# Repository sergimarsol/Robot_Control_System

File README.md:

# MSP430FR2355 Robot Control System

This repository contains the complete development of a robotic control system based on the MSP430FR2355 microcontroller. The project encompasses hardware design, embedded software development, real-time control implementation, and autonomous behavior strategies. All stages—from conceptual engineering to full system deployment—were carried out by a single author.

## Project Overview

The system enables robot control through multiple operational modes, leveraging a modular driver-based firmware architecture. It integrates input devices, actuators, and display components to provide both manual and autonomous control functionalities. The hardware was designed, assembled, debugged, and calibrated to ensure correct interaction among all peripherals.

### Control Modes
- **Joystick Mode**: Manual navigation using an analog joystick.
- **Light-Following Mode**: Robot movement directed toward the strongest detected light using LDR readings.
- **Line-Following Mode**: Ground sensor-based autonomous navigation via line detection.
- **Main Menu Interface**: LCD-driven user interface navigated using the joystick.

## Hardware Architecture

| Component | Description |
|-----------|-------------|
| MSP430FR2355 MCU | Core controller handling I2C, ADC, timers, GPIOs |
| 32.7KHz Crystal | Clock stabilization |
| SBW Connector | Programming and debugging interface |
| LCD 16x2 (I2C) | Displays system information and menu |
| Joystick | Directional input for manual control and navigation |
| LDR Sensors (ADC) | Detect light intensity for autonomous movement |
| Motor Driver (I2C) | Controls wheel motors for robot movement |
| RGB LEDs (I2C) | Status indication |
| ESP-01 Module (UART) | Planned Wi-Fi communication support |

## Software Architecture

The firmware was implemented with a modular structure to maximize maintainability and reusability.

| Module | Purpose |
|--------|---------|
| `main.c` | System initialization and main control loop |
| `timer.h` | Timer configuration, delays, millisecond counter ISR |
| `i2c.h` | I2C communication management and ISR |
| `lcd.h` | LCD initialization and text display functions |
| `leds.h` | RGB LED color control |
| `motors.h` | Motor control for direction and velocity |
| `joystick.h` | Joystick reading and movement triggering |
| `adc.h` | Light sensor acquisition and averaging |
| `sensors.h` | Line detection and autonomous path adjustment |

## Proposed Repository Structure

```
MSP430-Robot-Control-System
├── hardware/
│   ├── SergiMarsol_Gerber/                  # Gerber manufacturing outputs
│   ├── SergiMarsol_projecte_MISE.kicad_pro  # KiCad project file
│   ├── SergiMarsol_projecte_MISE.kicad_sch  # Schematic design
│   ├── SergiMarsol_projecte_MISE.kicad_pcb  # PCB layout
│   ├── SergiMarsol_projecte_MISE-backups/   # KiCad auto-backups
│   ├── SergiMarsol_projecte_MISE.kicad_prl  # KiCad project local settings
│   ├── fp-info-cache                        # Footprint cache
│   └── fp-lib-table                         # Footprint library table
├── firmware/
│   ├── ADC.c
│   ├── ADC.h
│   ├── i2c.c
│   ├── i2c.h
│   ├── joystick.c
│   ├── joystick.h
│   ├── lcd.c
│   ├── lcd.h
│   ├── leds.c
│   ├── leds.h
│   ├── motors.c
│   ├── motors.h
│   ├── sensors.c
│   ├── sensors.h
│   ├── timer.c
│   ├── timer.h
│   ├── main.c
│   ├── lnk_msp430fr2355.cmd                 # Linker command file
│   ├── Debug/                               # Compilation artifacts
│   └── targetConfigs/                       # MCU target configuration files
├── documents/
│   └── presentation.pdf                       # Final presentation of the project (in Catalan)
└── README.md
```

## Development Highlights

| Phase | Achievement |
|-------|------------|
| Concept Engineering | Block diagrams, requirements, planning |
| Hardware Implementation | Complete schematic design, assembly, correction of ADC pin assignments |
| Software Implementation | Driver-based structure enabling scalability |
| Debugging | Systematic validation using modular subsystem tests |
| Optional Expansion | UART-based Wi-Fi communication ready for future phases |

## Conclusion

The project demonstrates an end-to-end realization of an embedded robotic control system, showcasing microcontroller-based hardware integration, real-time firmware development, and autonomous control strategies. It serves as an excellent reference for modular embedded system design using the MSP430 ecosystem.

---

For future developments, planned features include remote control via Wi-Fi, telemetry reporting, and enhanced control algorithms such as PID for smoother autonomous navigation.

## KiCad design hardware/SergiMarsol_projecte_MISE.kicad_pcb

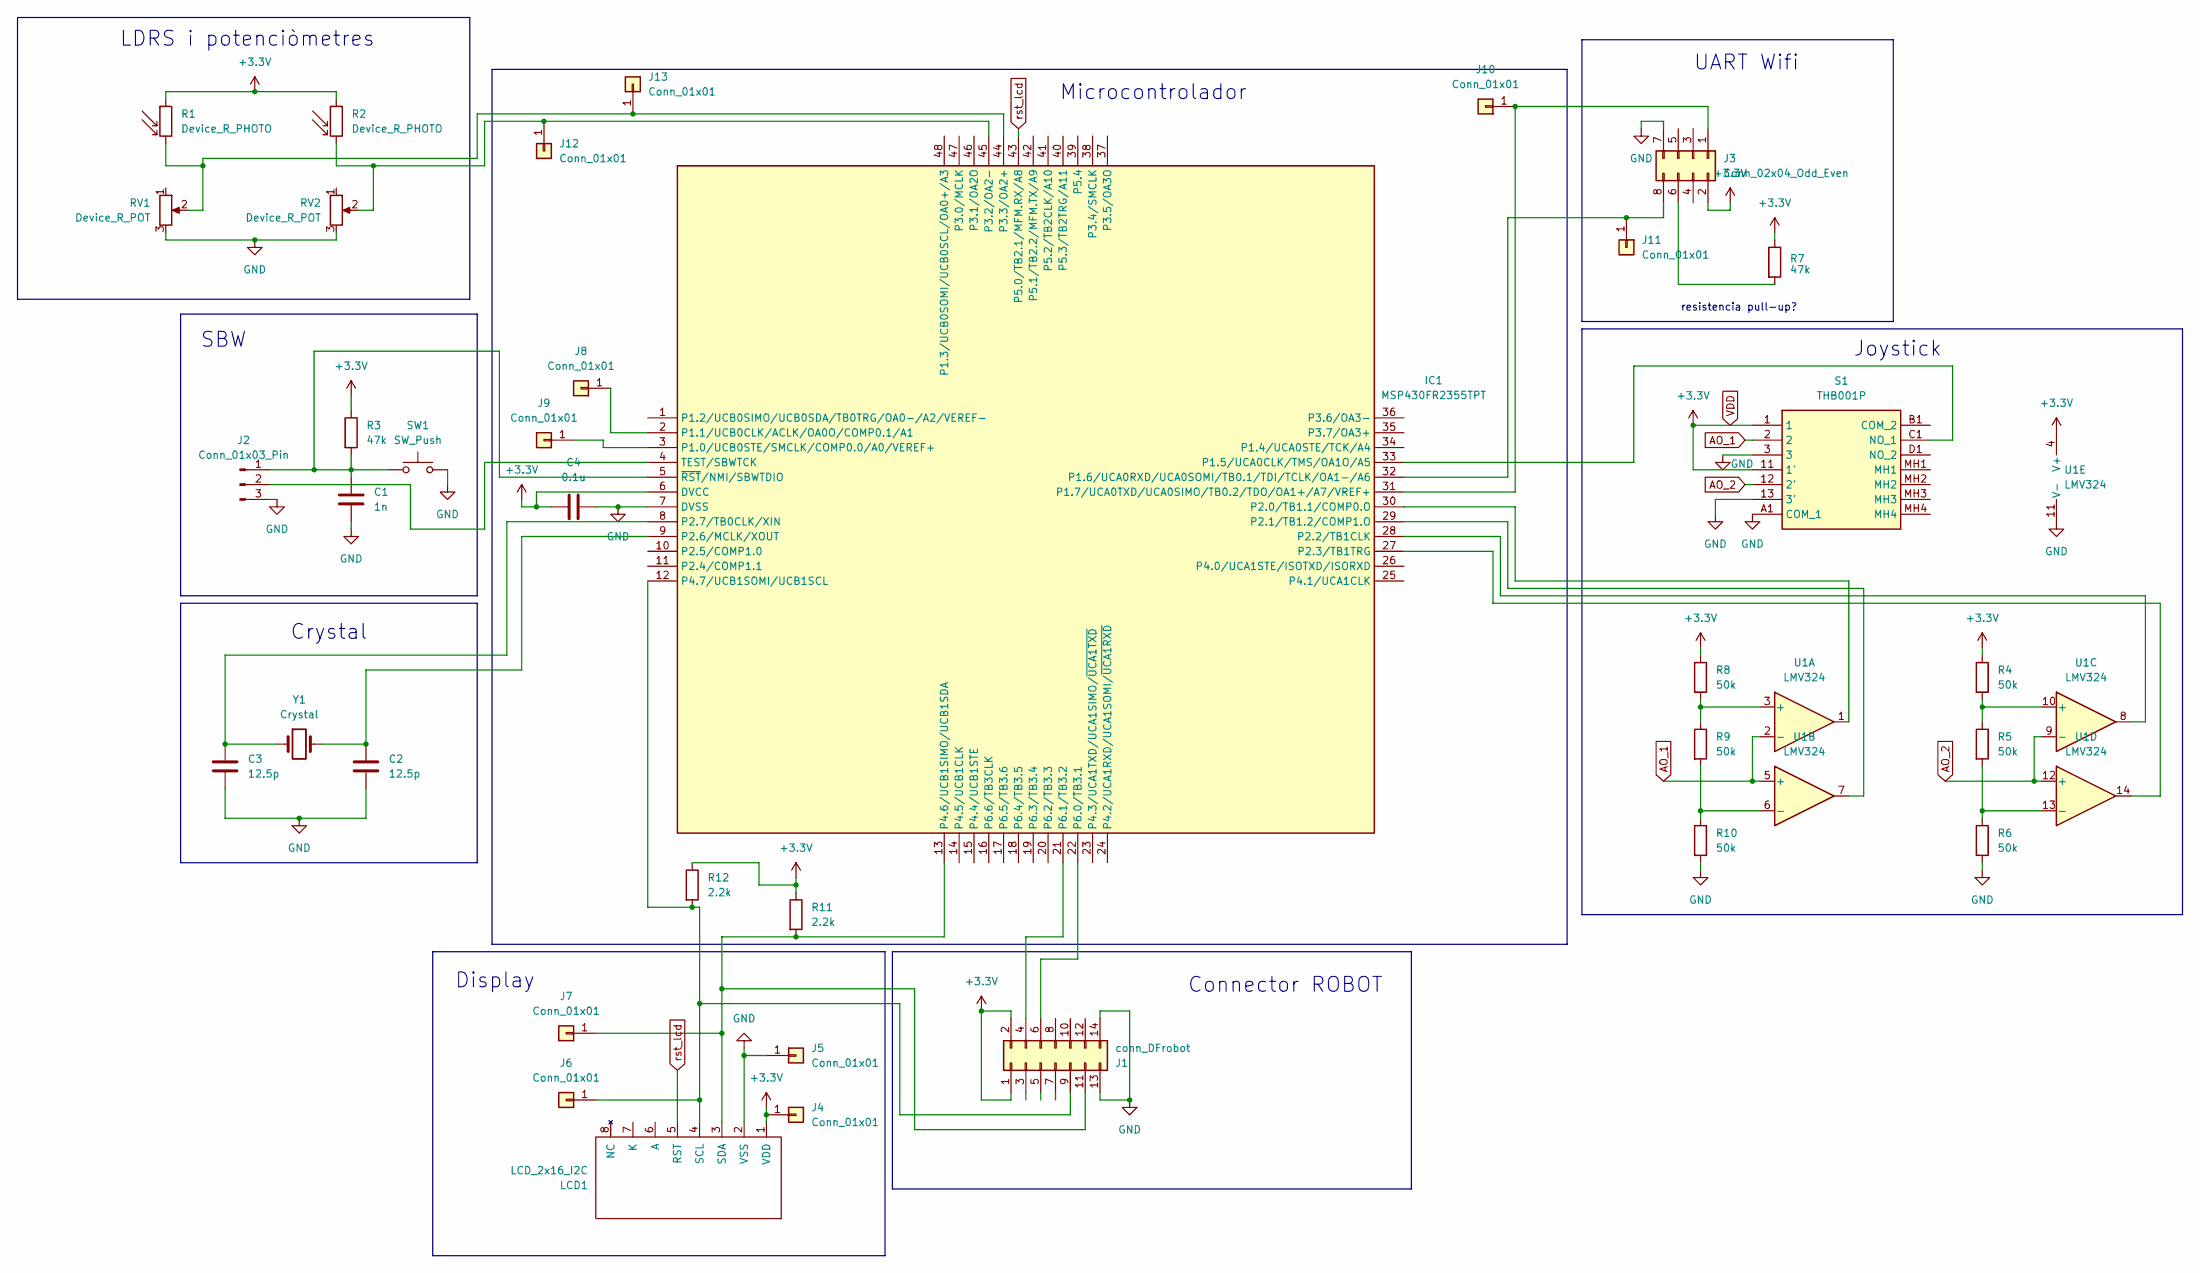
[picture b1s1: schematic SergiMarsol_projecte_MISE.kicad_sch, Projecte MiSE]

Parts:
C1: 1n; C_0805_2012Metric
C2, C3: 12.5p; C_0805_2012Metric
C4: 0.1u; C_0805_2012Metric
IC1: MSP430FR2355TPT; QFP50P900X900X160-48N; Manufacturer_Part_Number MSP430FR2355TPT; Mouser Part Number 595-MSP430FR2355TPT
J1: conn_DFrobot
J2: Conn_01x03_Pin; PinHeader_1x03_P2.54mm_Vertical
J3: Conn_02x04_Odd_Even; PinHeader_2x04_P2.54mm_Vertical
J4, J5, J6, J7, J8, J9, J10, J11, J12, J13: Conn_01x01; PinHeader_1x01_P2.54mm_Vertical
LCD1: LCD_2x16_I2C; LCD_2x16_I2C(Midas)
R1, R2: Device_R_PHOTO; LDR
R3, R7: 47k; R_0805_2012Metric
R4, R5, R6, R8, R9, R10: 50k; R_0805_2012Metric
R11, R12: 2.2k; R_0805_2012Metric
RV1, RV2: Device_R_POT; Trimmer_MiSE
S1: THB001P; Manufacturer_Part_Number THB001P; Mouser Part Number 611-THB001P
SW1: SW_Push; SW_PUSH_6mm_H4.3mm
U1: LMV324; SOIC127P600X175-14N
Y1: Crystal; XTAL_ECS-.327-8-14

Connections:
AO_1: S1.2, U1.2 (-), U1.5 (+)
AO_2: S1.12 (2'), U1.9 (-), U1.12 (+)
GND: C1.2, C2.2, C3.2, C4.2, IC1.7 (DVSS), J1.13, J1.14, J2.3, J3.7, J5.1, LCD1.2 (VSS), R6.2, R10.2, RV1.3, RV2.3, S1.3, S1.13 (3'), S1.A1 (COM_1), SW1.2, U1.11 (V-)
unnamed: IC1.3 (P1.0/UCB0STE/SMCLK/COMP0.0/A0/VEREF+), J9.1
unnamed: IC1.2 (P1.1/UCB0CLK/ACLK/OA0O/COMP0.1/A1), J8.1
unnamed: IC1.33 (P1.5/UCA0CLK/TMS/OA1O/A5), S1.C1 (NO_1)
unnamed: IC1.32 (P1.6/UCA0RXD/UCA0SOMI/TB0.1/TDI/TCLK/OA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), J3.8, J11.1
unnamed: IC1.31 (P1.7/UCA0TXD/UCA0SIMO/TB0.2/TDO/OA1+/A7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), J3.1, J10.1
unnamed: IC1.30 (P2.0/TB1.1/COMP0.O), U1.1
unnamed: IC1.29 (P2.1/TB1.2/COMP1.O), U1.7
unnamed: IC1.28 (P2.2/TB1CLK), U1.8
unnamed: IC1.27 (P2.3/TB1TRG), U1.14
unnamed: C2.1, IC1.9 (P2.6/MCLK/XOUT), Y1.2
unnamed: C3.1, IC1.8 (P2.7/TB0CLK/XIN), Y1.1
unnamed: IC1.45 (P3.2/OA2-), J12.1, R2.2, RV2.2
unnamed: IC1.44 (P3.3/OA2+), J13.1, R1.2, RV1.2
unnamed: IC1.13 (P4.6/UCB1SIMO/UCB1SDA), J1.11, J7.1, LCD1.3 (SDA), R11.2
unnamed: IC1.12 (P4.7/UCB1SOMI/UCB1SCL), J1.9, J6.1, LCD1.4 (SCL), R12.2
unnamed: IC1.22 (P6.0/TB3.1), J1.6
unnamed: IC1.21 (P6.1/TB3.2), J1.4
unnamed: IC1.4 (TEST/SBWTCK), J2.2
unnamed: C1.1, IC1.5 (~RST/NMI/SBWTDIO), J2.1, R3.2, SW1.1
unnamed: J3.6, R7.2
unnamed: R8.2, R9.1, U1.3 (+)
unnamed: R9.2, R10.1, U1.6 (-)
unnamed: R4.2, R5.1, U1.10 (+)
unnamed: R5.2, R6.1, U1.13 (-)
VDD: C4.1, IC1.6 (DVCC), J1.1, J1.2, J3.2, J4.1, LCD1.1 (VDD), R1.1, R2.1, R3.1, R4.1, R7.1, R8.1, R11.1, R12.1, S1.1, S1.11 (1'), U1.4 (V+)
rst_lcd: IC1.43 (P5.0/TB2.1/MFM.RX/A8), LCD1.5 (RST)

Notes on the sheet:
UART Wifi
Crystal
Display
SBW
LDRS i potenciòmetres
resistencia pull-up?
Connector ROBOT
Microcontrolador
Joystick

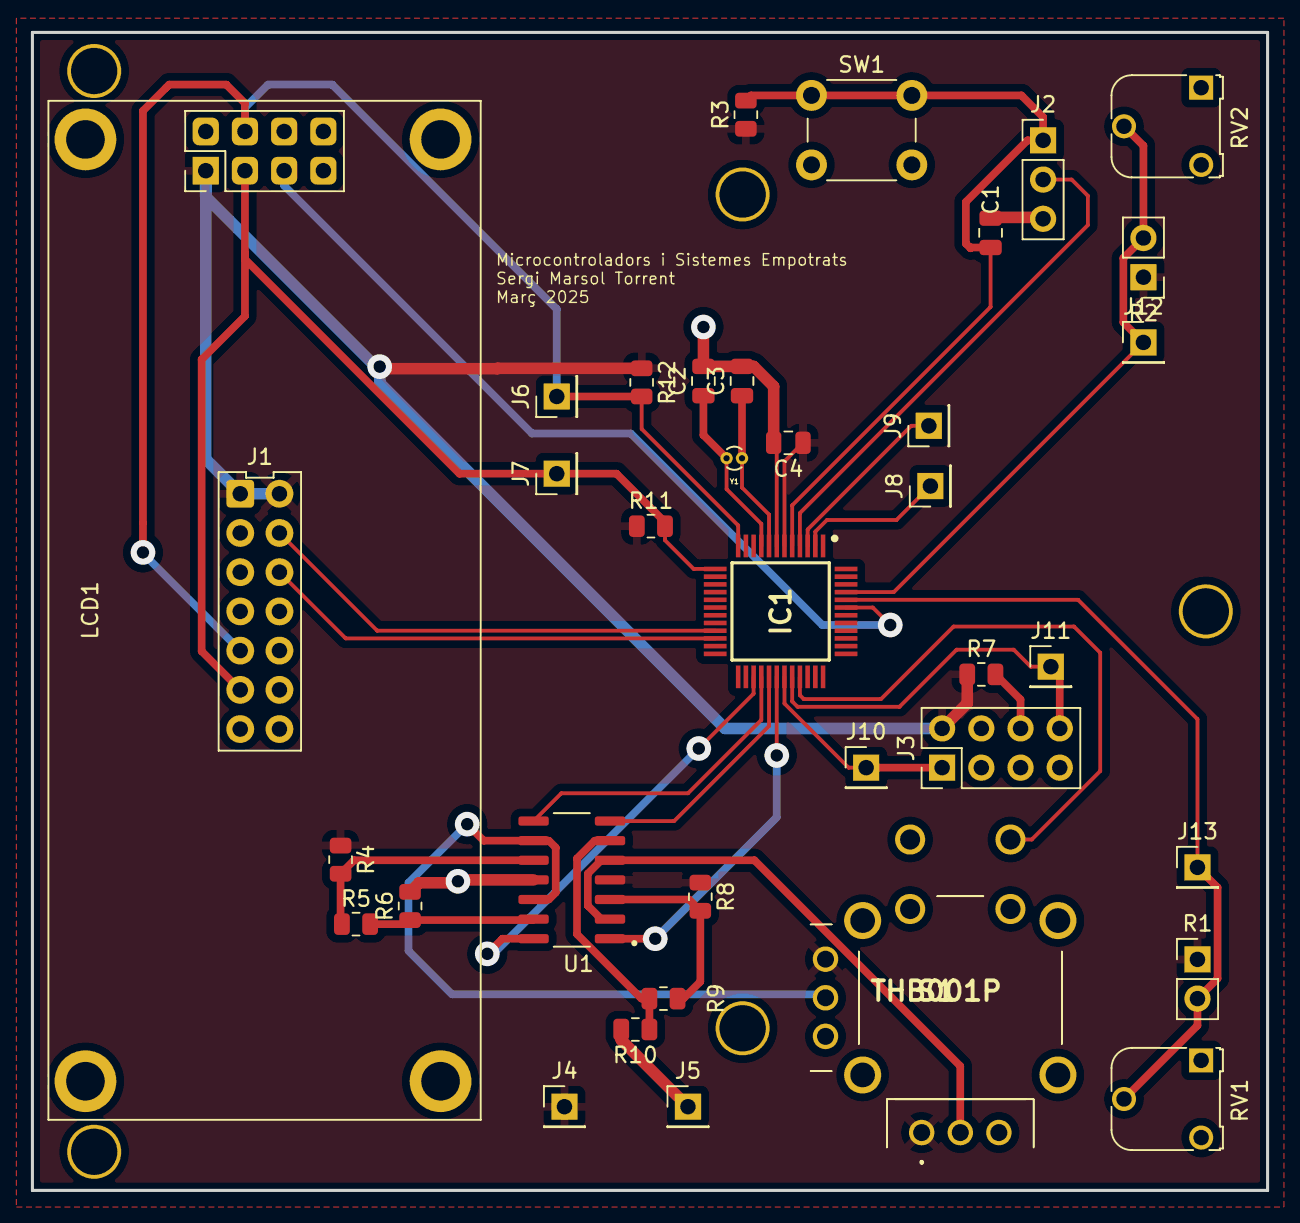
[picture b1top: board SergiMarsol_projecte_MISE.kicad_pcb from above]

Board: 2 copper layers, 80.0 x 75.0 mm, 37 parts (0 on the bottom side), 29 nets.
